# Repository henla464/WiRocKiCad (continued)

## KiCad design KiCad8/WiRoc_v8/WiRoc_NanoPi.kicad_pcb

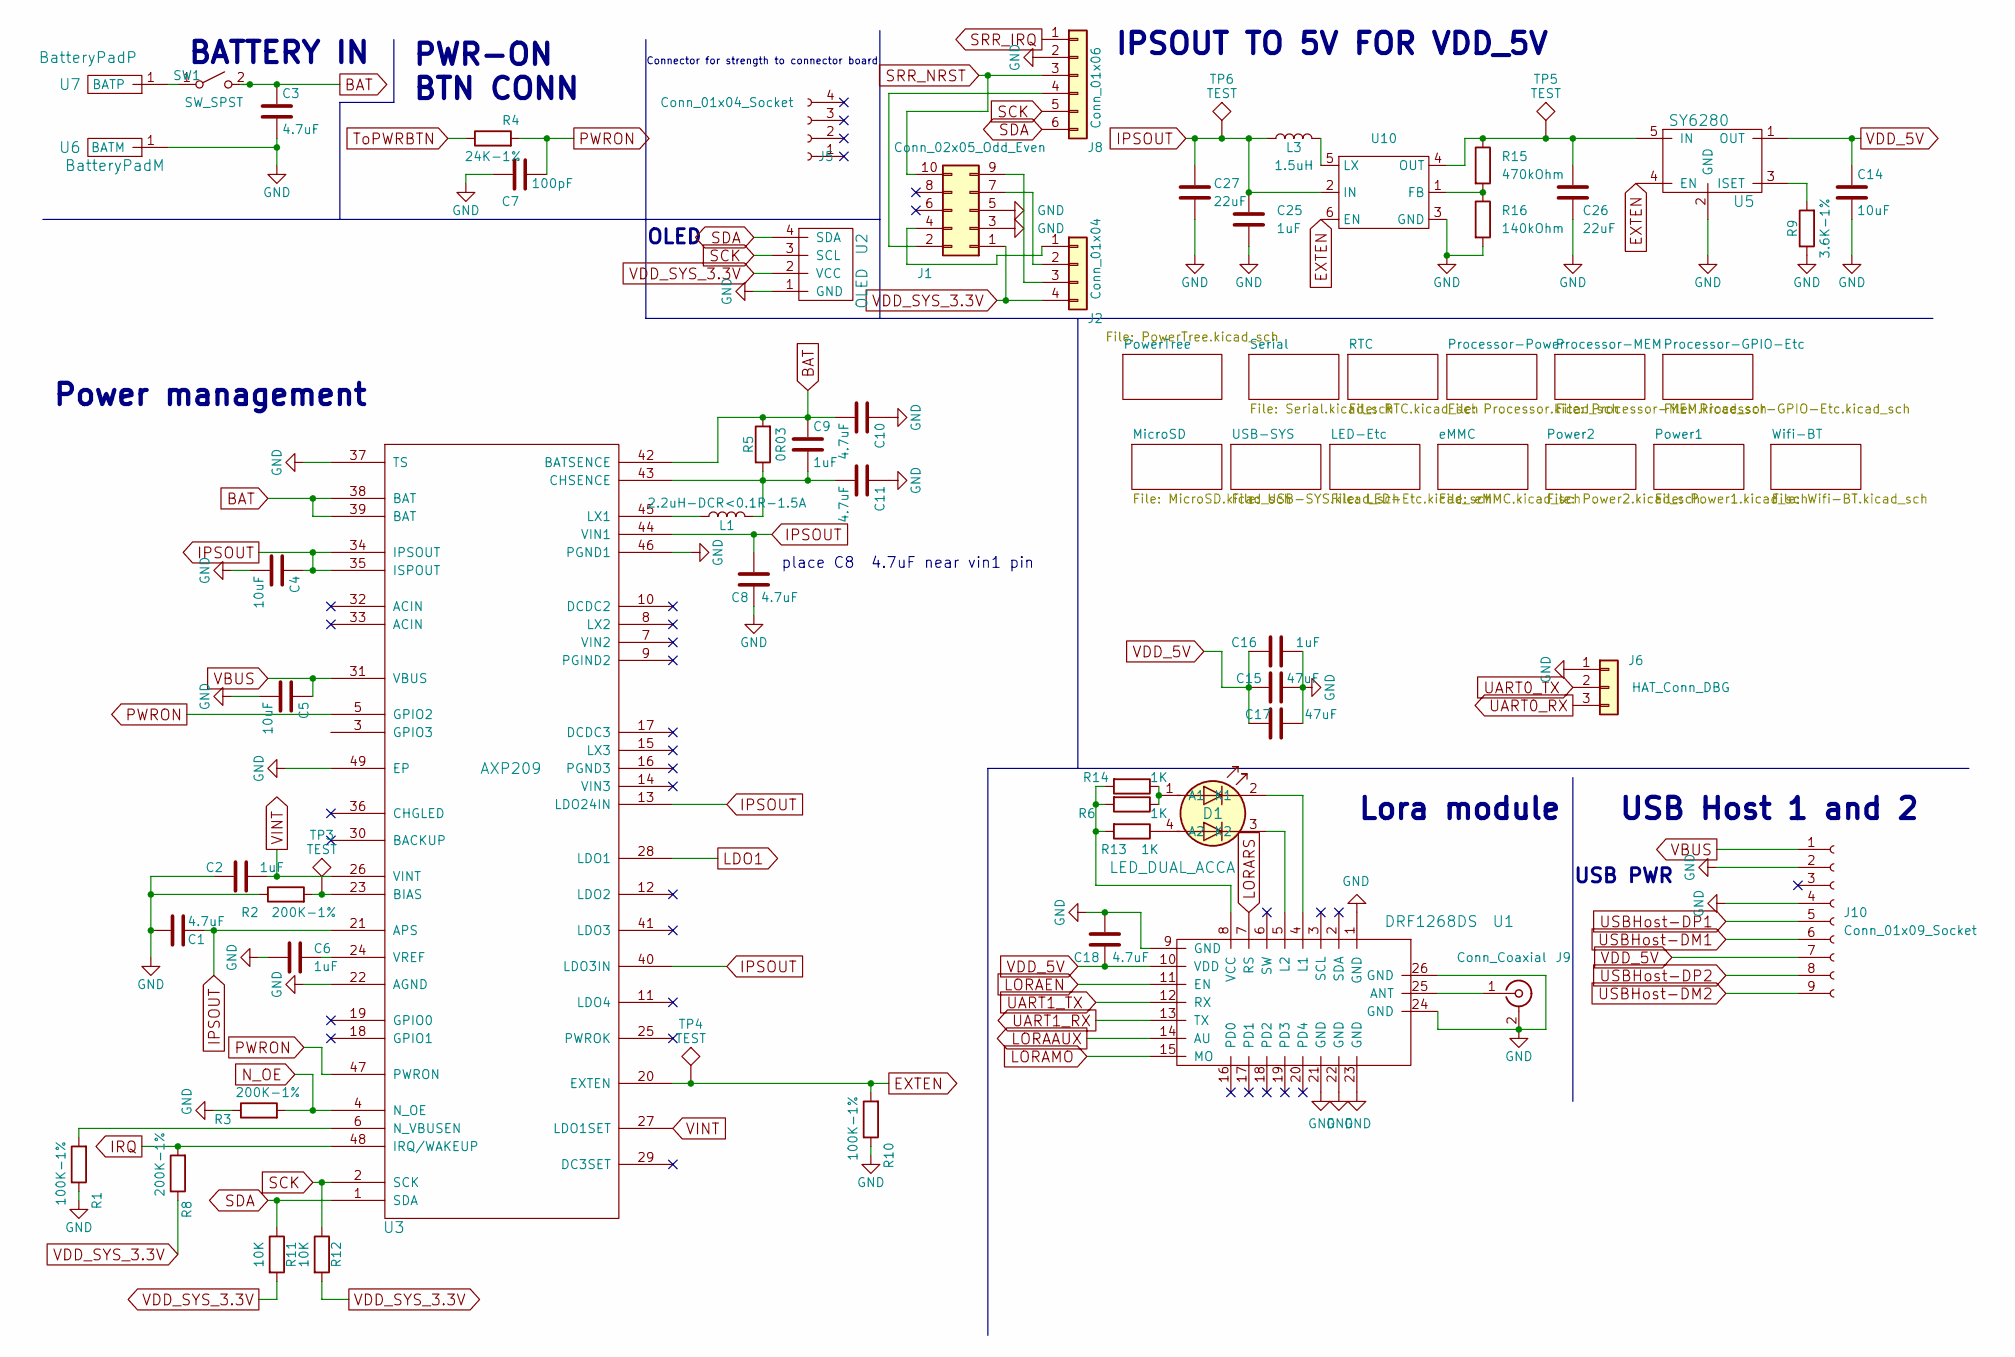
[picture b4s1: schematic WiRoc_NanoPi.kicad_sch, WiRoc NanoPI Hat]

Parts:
C1, C3, C8, C10, C11, C18: 4.7uF; C_0402_1005Metric; ManufacturerPartNumber CL10A475KO8NNNC; LCSC Part # C19666
C2, C6, C9, C16, C25: 1uF; C_0402_1005Metric; ManufacturerPartNumber CL10A105KB8NNNC; LCSC Part # C15849
C4, C5, C14: 10uF; C_0402_1005Metric; ManufacturerPartNumber CL10A106KP8NNNC; LCSC Part # C19702
C7: 100pF; C_0402_1005Metric; ManufacturerPartNumber CL10C101JB8NNNC; LCSC Part # C14858
C15, C17: 47uF; C_1206_3216Metric; ManufacturerPartNumber CL31A476MPHNNNE; LCSC Part # C96123
C26, C27: 22uF; C_0402_1005Metric; PartNo GRM188R61A226ME15D; LCSC Part # C84419
D1: LED_DUAL_ACCA; LED_Dual_1.7_1.6; ManufacturerPartNumber HL-PCB-1617S9FH203BC; LCSC Part # C513363
J1: Conn_02x05_Odd_Even; PinHeader_2x05_P1.27mm_Vertical
J2: Conn_01x04; PinHeader_1x04_P1.27mm_Horizontal
J5: Conn_01x04_Socket; PinSocket_1x04_P1.27mm_Vertical
J6: HAT_Conn_DBG; Pin_Header_Straight_1x03_Pitch2.54mm; ManufacturerPartNumber 2.54mm 1x40P
J8: Conn_01x06; PinHeader_1x06_P1.27mm_Horizontal
J9: Conn_Coaxial; SMA_Amphenol_901-143_Horizontal
J10: Conn_01x09_Socket; PinSocket_1x09_P1.27mm_Vertical
L1: 2.2uH-DCR<0.1R-1.5A; Inductor_SLW4018; ManufacturerPartNumber SLW4018S2R2MST; LCSC Part # C206341
L3: 1.5uH; Inductor_SLW4018; PartNo SLW4020S1R5MST; LCSC Part # C206395
R1, R10: 100K-1%; R_0402_1005Metric; ManufacturerPartNumber 0603WAF1003T5E; LCSC Part # C25803
R2, R3, R8: 200K-1%; R_0402_1005Metric; ManufacturerPartNumber 0603WAF2003T5E; LCSC Part # C25811
R4: 24K-1%; R_0402_1005Metric; ManufacturerPartNumber 0603WAF2402T5E; LCSC Part # C23352
R5: 0R03; R_0805_2012Metric; ManufacturerPartNumber 0805W4F300MT5E; LCSC Part # C247605
R6, R13, R14: 1K; R_0402_1005Metric; ManufacturerPartNumber 0603WAJ0102T5E; LCSC Part # C21190
R9: 3.6K-1%; R_0402_1005Metric; ManufacturerPartNumber 0603WAF3601T5E; LCSC Part # C22980
R11, R12: 10K; R_0402_1005Metric; ManufacturerPartNumber 0603WAF1002T5E; LCSC Part # C25804
R15: 470kOhm; R_0402_1005Metric; PartNo HPCR0603F470KK9; LCSC Part # C23178
R16: 140kOhm; R_0402_1005Metric; PartNo 0603WAF140KT5E; LCSC Part # C321721
SW1: SW_SPST; Pin_Header_Straight_1x02_Pitch2.54mm; ManufacturerPartNumber 2.54mm 1x40P
TP3, TP4, TP5, TP6: TEST; TestPoint_Pad_D1.0mm
U1: DRF1268DS
U2: OLED; CONN_OLED_TWI-Socket_Strip_Straight_1x04_Pitch2.54mm; ManufacturerPartNumber 2.54mm 1x40P
U3: AXP209; qfn48_6x6mm_Pitch0.4mm; ManufacturerPartNumber AXP209; LCSC Part # C2997895
U5: SY6280; SOT-23-5; ManufacturerPartNumber SY6280AAC; LCSC Part # C55136
U6: BatteryPadM; BatteryPad
U7: BatteryPadP; BatteryPadThinner
U10: TSOT-23-6; PartNo SY7069ADC; LCSC Part # C207630

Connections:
BAT: C3.1, C9.1, C10.2, R5.2, SW1.2 (B), U3.38 (BAT), U3.39 (BAT), U3.42 (BATSENCE)
EXTEN: R10.2, TP4.1, U3.20 (EXTEN), U5.4 (EN), U10.6 (EN)
GND: C1.2, C2.2, C3.2, C4.2, C5.2, C6.2, C7.1, C8.1, C10.1, C11.1, C14.2, C15.1, C16.2, C17.1, C18.2, C25.2, C26.2, C27.2, J1.3, J1.5, J6.1, J8.2, J9.2 (Ext), J10.2, J10.4, R1.1, R2.1, R3.1, R9.1, R10.1, R16.2, U1.1 (GND), U1.9 (GND), U1.21 (GND), U1.22 (GND), U1.23 (GND), U1.24 (GND), U1.26 (GND), U2.1 (GND), U3.22 (AGND), U3.37 (TS), U3.46 (PGND1), U3.49 (EP), U5.2 (GND), U6.1 (BATM), U10.3 (GND); also elsewhere on the board
IPSOUT: C1.1, C4.1, C8.2, C25.1, C27.1, L3.1, TP6.1, U3.13 (LDO24IN), U3.21 (APS), U3.34 (IPSOUT), U3.35 (ISPOUT), U3.40 (LDO3IN), U3.44 (VIN1), U10.2 (IN)
IRQ: R8.2, U3.48 (IRQ/WAKEUP); also elsewhere on the board
LDO1: U3.28 (LDO1); also elsewhere on the board
LORAAUX: U1.14 (AU); also elsewhere on the board
LORAEN: U1.11 (EN); also elsewhere on the board
LORAMO: U1.15 (MO); also elsewhere on the board
LORARS: U1.7 (RS); also elsewhere on the board
N_OE: R3.2, U3.4 (N_OE); also elsewhere on the board
unnamed: D1.1 (A1), R6.1, R14.1
unnamed: D1.4 (A2), R13.1
unnamed: D1.2 (K1), U1.4 (L1)
unnamed: D1.3 (K2), U1.5 (L2)
unnamed: J1.2, J8.4
unnamed: J1.4, J2.1
unnamed: J1.7, J2.2
unnamed: J1.9, J2.3
unnamed: J9.1 (In), U1.25 (ANT)
unnamed: SW1.1 (A), U7.1 (BATP)
unnamed: R6.2, R13.2, R14.2, U1.8 (VCC)
unnamed: R2.2, TP3.1, U3.23 (BIAS)
unnamed: C9.2, C11.2, L1.2, R5.1, U3.43 (CHSENCE)
unnamed: L1.1, U3.45 (LX1)
unnamed: R1.2, U3.6 (N_VBUSEN)
unnamed: C6.1, U3.24 (VREF)
unnamed: R9.2, U5.3 (ISET)
unnamed: R15.2, R16.1, U10.1 (FB)
unnamed: L3.2, U10.5 (LX)
unnamed: C26.1, R15.1, TP5.1, U5.5 (IN), U10.4 (OUT)
PWRON: C7.2, R4.2, U3.5 (GPIO2), U3.47 (PWRON)
SCK: J8.5, R12.1, U2.3 (SCL), U3.2 (SCK); also elsewhere on the board
SDA: J8.6, R11.1, U2.4 (SDA), U3.1 (SDA); also elsewhere on the board
SRR_IRQ: J8.1; also elsewhere on the board
SRR_NRST: J1.10, J8.3; also elsewhere on the board
ToPWRBTN: R4.1; also elsewhere on the board
UART0_RX: J6.3; also elsewhere on the board
UART0_TX: J6.2; also elsewhere on the board
UART1_RX: U1.13 (TX); also elsewhere on the board
UART1_TX: U1.12 (RX); also elsewhere on the board
USBHost-DM1: J10.6; also elsewhere on the board
USBHost-DM2: J10.9; also elsewhere on the board
USBHost-DP1: J10.5; also elsewhere on the board
USBHost-DP2: J10.8; also elsewhere on the board
VBUS: C5.1, J10.1, U3.31 (VBUS)
VDD_5V: C14.1, C15.2, C16.1, C17.2, C18.1, J10.7, U1.10 (VDD), U5.1 (OUT); also elsewhere on the board
VDD_SYS_3.3V: J1.1, J2.4, R8.1, R11.2, R12.2, U2.2 (VCC); also elsewhere on the board
VINT: C2.1, U3.26 (VINT), U3.27 (LDO1SET)

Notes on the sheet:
place C8 4.7uF near vin1 pin
USB PWR
Lora module
IPSOUT TO 5V FOR VDD_5V
PWR-ON BTN CONN
Power management
OLED
Connector for strength to connector board
USB Host 1 and 2
BATTERY IN

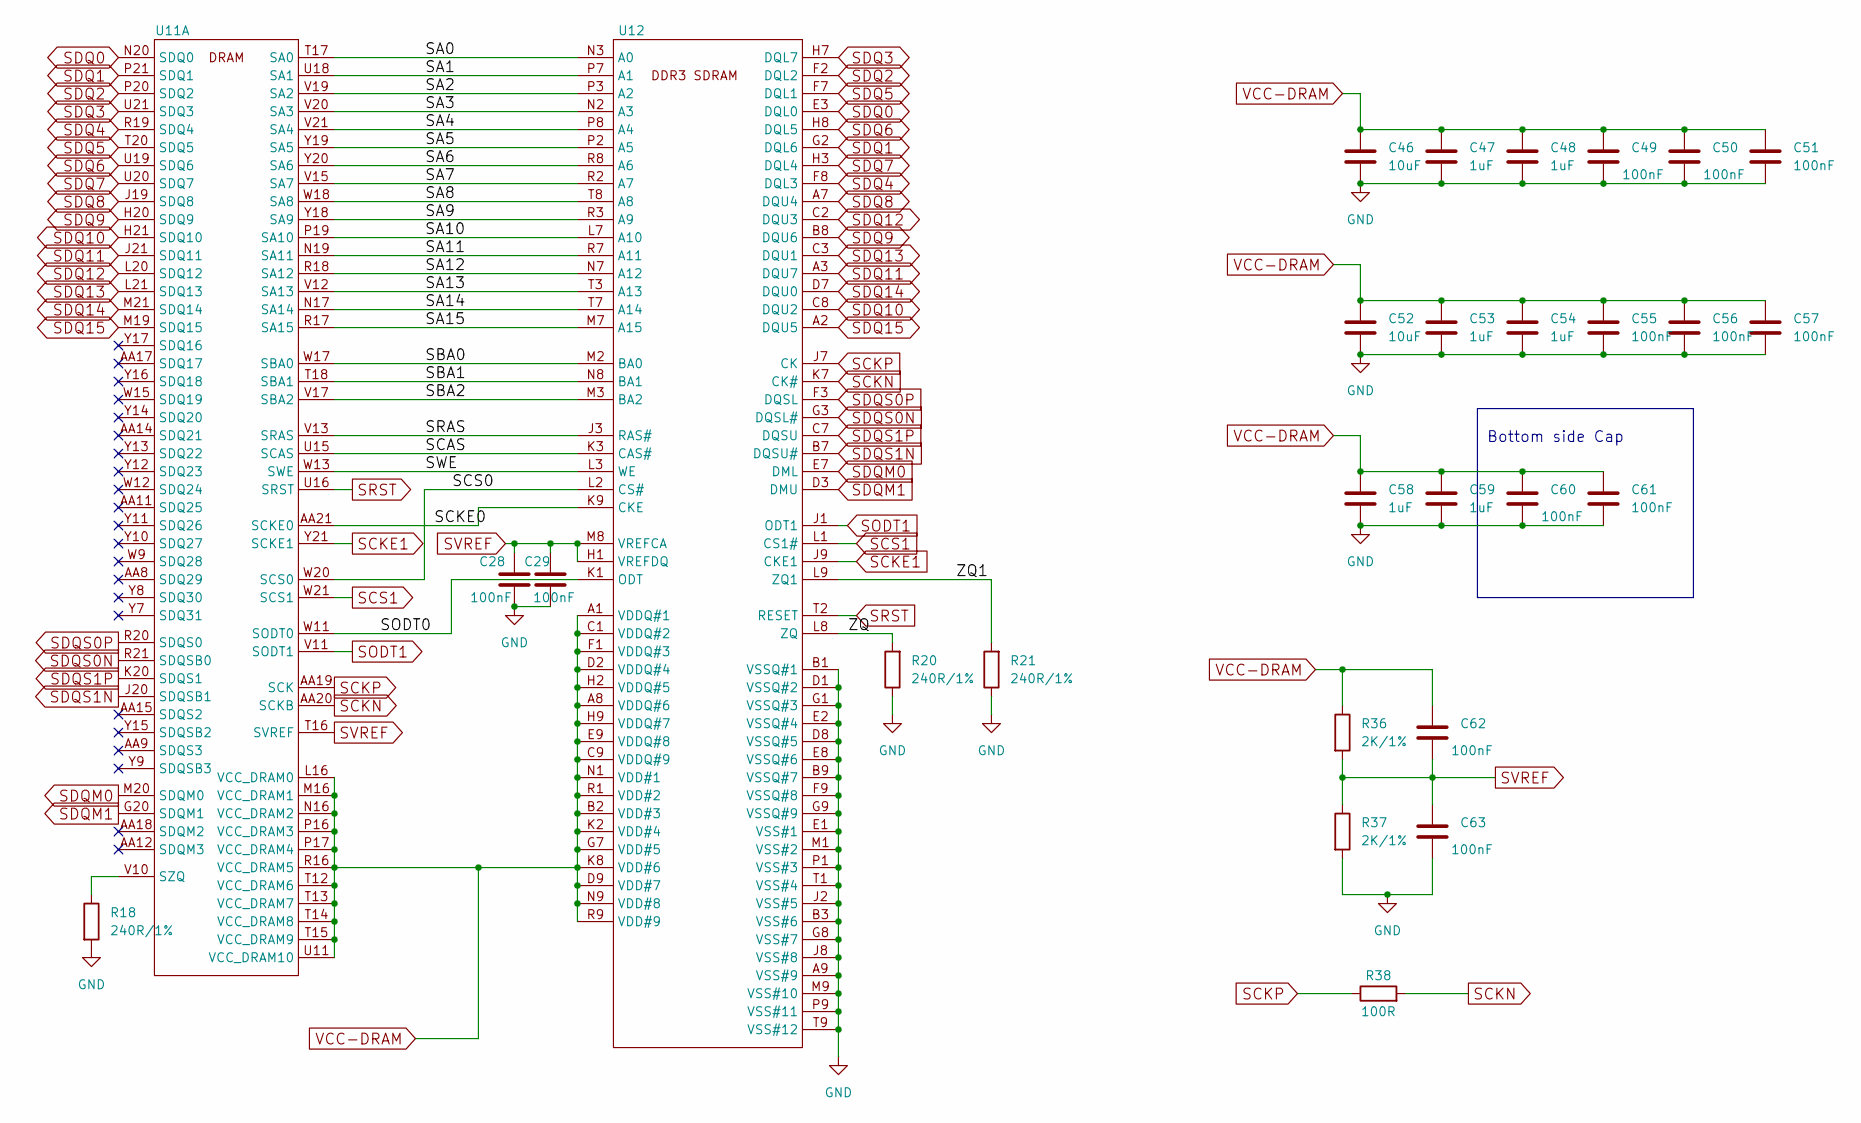
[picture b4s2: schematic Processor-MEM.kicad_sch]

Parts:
C28, C29, C49, C50, C51, C55, C56, C57, C60, C61, C62, C63: 100nF; C_0402_1005Metric
C46, C52: 10uF; C_0402_1005Metric
C47, C48, C53, C54, C58, C59: 1uF; C_0402_1005Metric
R18, R20, R21: 240R/1%; R_0402_1005Metric
R36, R37: 2K/1%; R_0402_1005Metric
R38: 100R; R_0402_1005Metric
U11: BGA-347_21x21_14.0x14.0mm
U12: BGA-96_9.0x13.0mm_Layout2x3x16_P0.8mm

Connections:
/Processor-MEM/SA0: U11.T17 (SA0), U12.N3 (A0)
/Processor-MEM/SA1: U11.U18 (SA1), U12.P7 (A1)
/Processor-MEM/SA2: U11.V19 (SA2), U12.P3 (A2)
/Processor-MEM/SA3: U11.V20 (SA3), U12.N2 (A3)
/Processor-MEM/SA4: U11.V21 (SA4), U12.P8 (A4)
/Processor-MEM/SA5: U11.Y19 (SA5), U12.P2 (A5)
/Processor-MEM/SA6: U11.Y20 (SA6), U12.R8 (A6)
/Processor-MEM/SA7: U11.V15 (SA7), U12.R2 (A7)
/Processor-MEM/SA8: U11.W18 (SA8), U12.T8 (A8)
/Processor-MEM/SA9: U11.Y18 (SA9), U12.R3 (A9)
/Processor-MEM/SA10: U11.P19 (SA10), U12.L7 (A10)
/Processor-MEM/SA11: U11.N19 (SA11), U12.R7 (A11)
/Processor-MEM/SA12: U11.R18 (SA12), U12.N7 (A12)
/Processor-MEM/SA13: U11.V12 (SA13), U12.T3 (A13)
/Processor-MEM/SA14: U11.N17 (SA14), U12.T7 (A14)
/Processor-MEM/SA15: U11.R17 (SA15), U12.M7 (A15)
/Processor-MEM/SBA0: U11.W17 (SBA0), U12.M2 (BA0)
/Processor-MEM/SBA1: U11.T18 (SBA1), U12.N8 (BA1)
/Processor-MEM/SBA2: U11.V17 (SBA2), U12.M3 (BA2)
/Processor-MEM/SCAS: U11.U15 (SCAS), U12.K3 (CAS#)
/Processor-MEM/SCKE0: U11.AA21 (SCKE0), U12.K9 (CKE)
/Processor-MEM/SCS0: U11.W20 (SCS0), U12.L2 (CS#)
/Processor-MEM/SODT0: U11.W11 (SODT0), U12.K1 (ODT)
/Processor-MEM/SRAS: U11.V13 (SRAS), U12.J3 (RAS#)
/Processor-MEM/SWE: U11.W13 (SWE), U12.L3 (WE)
/Processor-MEM/ZQ: R20.2, U12.L8 (ZQ)
/Processor-MEM/ZQ1: R21.2, U12.L9 (ZQ1)
GND: C28.2, C29.2, C46.2, C47.2, C48.2, C49.2, C50.2, C51.2, C52.2, C53.2, C54.2, C55.2, C56.2, C57.2, C58.2, C59.2, C60.2, C61.2, C63.2, R18.2, R20.1, R21.1, R37.2, U12.A9 (VSS#9), U12.B1 (VSSQ#1), U12.B3 (VSS#6), U12.B9 (VSSQ#7), U12.D1 (VSSQ#2), U12.D8 (VSSQ#5), U12.E1 (VSS#1), U12.E2 (VSSQ#4), U12.E8 (VSSQ#6), U12.F9 (VSSQ#8), U12.G1 (VSSQ#3), U12.G8 (VSS#7), U12.G9 (VSSQ#9), U12.J2 (VSS#5), U12.J8 (VSS#8), U12.M1 (VSS#2), U12.M9 (VSS#10), U12.P1 (VSS#3), U12.P9 (VSS#11), U12.T1 (VSS#4), U12.T9 (VSS#12); also elsewhere on the board
unnamed: R18.1, U11.V10 (SZQ)
SCKE1: U11.Y21 (SCKE1), U12.J9 (CKE1)
SCKN: R38.2, U11.AA20 (SCKB), U12.K7 (CK#)
SCKP: R38.1, U11.AA19 (SCK), U12.J7 (CK)
SCS1: U11.W21 (SCS1), U12.L1 (CS1#)
SDQ0: U11.N20 (SDQ0), U12.E3 (DQL0)
SDQ1: U11.P21 (SDQ1), U12.G2 (DQL6)
SDQ2: U11.P20 (SDQ2), U12.F2 (DQL2)
SDQ3: U11.U21 (SDQ3), U12.H7 (DQL7)
SDQ4: U11.R19 (SDQ4), U12.F8 (DQL3)
SDQ5: U11.T20 (SDQ5), U12.F7 (DQL1)
SDQ6: U11.U19 (SDQ6), U12.H8 (DQL5)
SDQ7: U11.U20 (SDQ7), U12.H3 (DQL4)
SDQ8: U11.J19 (SDQ8), U12.A7 (DQU4)
SDQ9: U11.H20 (SDQ9), U12.B8 (DQU6)
SDQ10: U11.H21 (SDQ10), U12.C8 (DQU2)
SDQ11: U11.J21 (SDQ11), U12.A3 (DQU7)
SDQ12: U11.L20 (SDQ12), U12.C2 (DQU3)
SDQ13: U11.L21 (SDQ13), U12.C3 (DQU1)
SDQ14: U11.M21 (SDQ14), U12.D7 (DQU0)
SDQ15: U11.M19 (SDQ15), U12.A2 (DQU5)
SDQM0: U11.M20 (SDQM0), U12.E7 (DML)
SDQM1: U11.G20 (SDQM1), U12.D3 (DMU)
SDQS0N: U11.R21 (SDQSB0), U12.G3 (DQSL#)
SDQS0P: U11.R20 (SDQS0), U12.F3 (DQSL)
SDQS1N: U11.J20 (SDQSB1), U12.B7 (DQSU#)
SDQS1P: U11.K20 (SDQS1), U12.C7 (DQSU)
SODT1: U11.V11 (SODT1), U12.J1 (ODT1)
SRST: U11.U16 (SRST), U12.T2 (RESET)
SVREF: C28.1, C29.1, C62.2, C63.1, R36.2, R37.1, U11.T16 (SVREF), U12.H1 (VREFDQ), U12.M8 (VREFCA)
VCC-DRAM: C46.1, C47.1, C48.1, C49.1, C50.1, C51.1, C52.1, C53.1, C54.1, C55.1, C56.1, C57.1, C58.1, C59.1, C60.1, C61.1, C62.1, R36.1, U11.L16 (VCC_DRAM0), U11.M16 (VCC_DRAM1), U11.N16 (VCC_DRAM2), U11.P16 (VCC_DRAM3), U11.P17 (VCC_DRAM4), U11.R16 (VCC_DRAM5), U11.T12 (VCC_DRAM6), U11.T13 (VCC_DRAM7), U11.T14 (VCC_DRAM8), U11.T15 (VCC_DRAM9), U11.U11 (VCC_DRAM10), U12.A1 (VDDQ#1), U12.A8 (VDDQ#6), U12.B2 (VDD#3), U12.C1 (VDDQ#2), U12.C9 (VDDQ#9), U12.D2 (VDDQ#4), U12.D9 (VDD#7), U12.E9 (VDDQ#8), U12.F1 (VDDQ#3), U12.G7 (VDD#5), U12.H2 (VDDQ#5), U12.H9 (VDDQ#7), U12.K2 (VDD#4), U12.K8 (VDD#6), U12.N1 (VDD#1), U12.N9 (VDD#8), U12.R1 (VDD#2), U12.R9 (VDD#9); also elsewhere on the board

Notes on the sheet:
Bottom side Cap

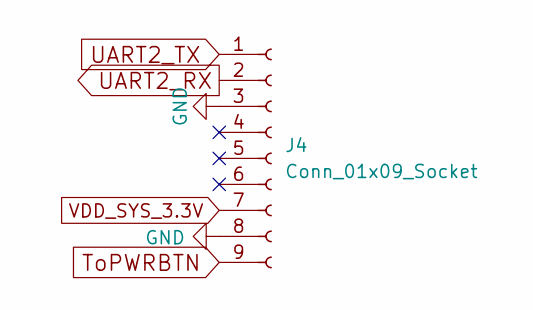
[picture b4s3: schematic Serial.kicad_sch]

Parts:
J4: Conn_01x09_Socket; PinSocket_1x09_P1.27mm_Vertical

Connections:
GND: J4.3, J4.8; also elsewhere on the board
ToPWRBTN: J4.9; also elsewhere on the board
UART2_RX: J4.2; also elsewhere on the board
UART2_TX: J4.1; also elsewhere on the board
VDD_SYS_3.3V: J4.7; also elsewhere on the board

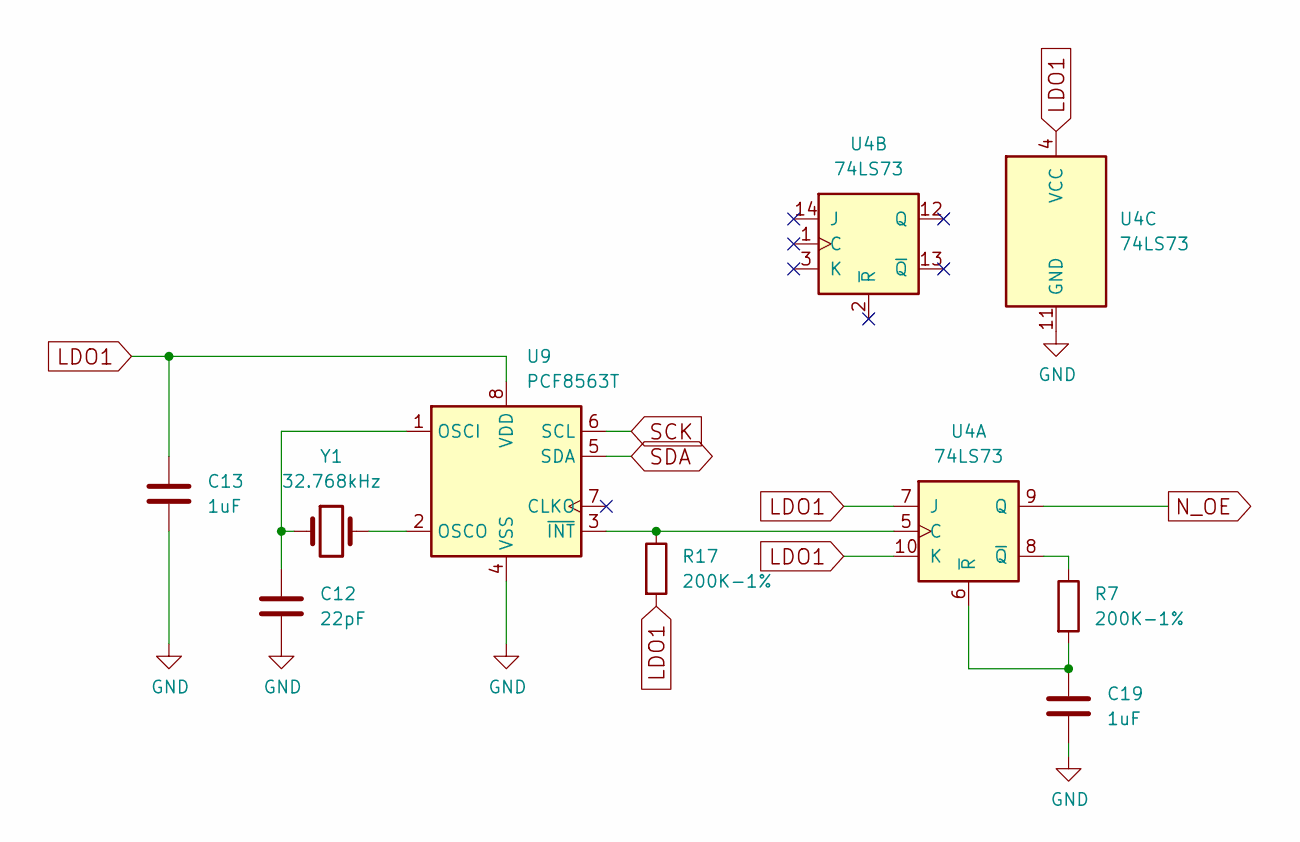
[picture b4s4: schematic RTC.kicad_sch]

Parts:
C12: 22pF; C_0402_1005Metric; ManufacturerPartNumber GRM155R71C223JA01D; LCSC Part # C1555
C13, C19: 1uF; C_0402_1005Metric; ManufacturerPartNumber CL10A105KB8NNNC; LCSC Part # C15849
R7, R17: 200K-1%; R_0402_1005Metric; ManufacturerPartNumber 0603WAF2003T5E; LCSC Part # C25811
U4: 74LS73; SOIC-14_3.9x8.7mm_P1.27mm; ManufacturerPartNumber CD74HC73M96; LCSC Part # C350539
U9: PCF8563T; SOIC-8_3.9x4.9mm_P1.27mm; ManufacturerPartNumber PCF8563T/5,518; LCSC Part # C7440
Y1: 32.768kHz; SMD3215-2P; ManufacturerPartNumber Q13FC1350000400; LCSC Part # C32346

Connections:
GND: C12.2, C13.2, C19.2, U4.11 (GND), U9.4 (VSS); also elsewhere on the board
LDO1: C13.1, R17.2, U4.4 (VCC), U4.7 (J), U4.10 (K), U9.8 (VDD); also elsewhere on the board
N_OE: U4.9 (Q); also elsewhere on the board
unnamed: R17.1, U4.5 (C), U9.3 (~INT)
unnamed: R7.1, U4.8 (~Q)
unnamed: C19.1, R7.2, U4.6 (~R)
unnamed: C12.1, U9.1 (OSCI), Y1.1
unnamed: U9.2 (OSCO), Y1.2
SCK: U9.6 (SCL); also elsewhere on the board
SDA: U9.5 (SDA); also elsewhere on the board

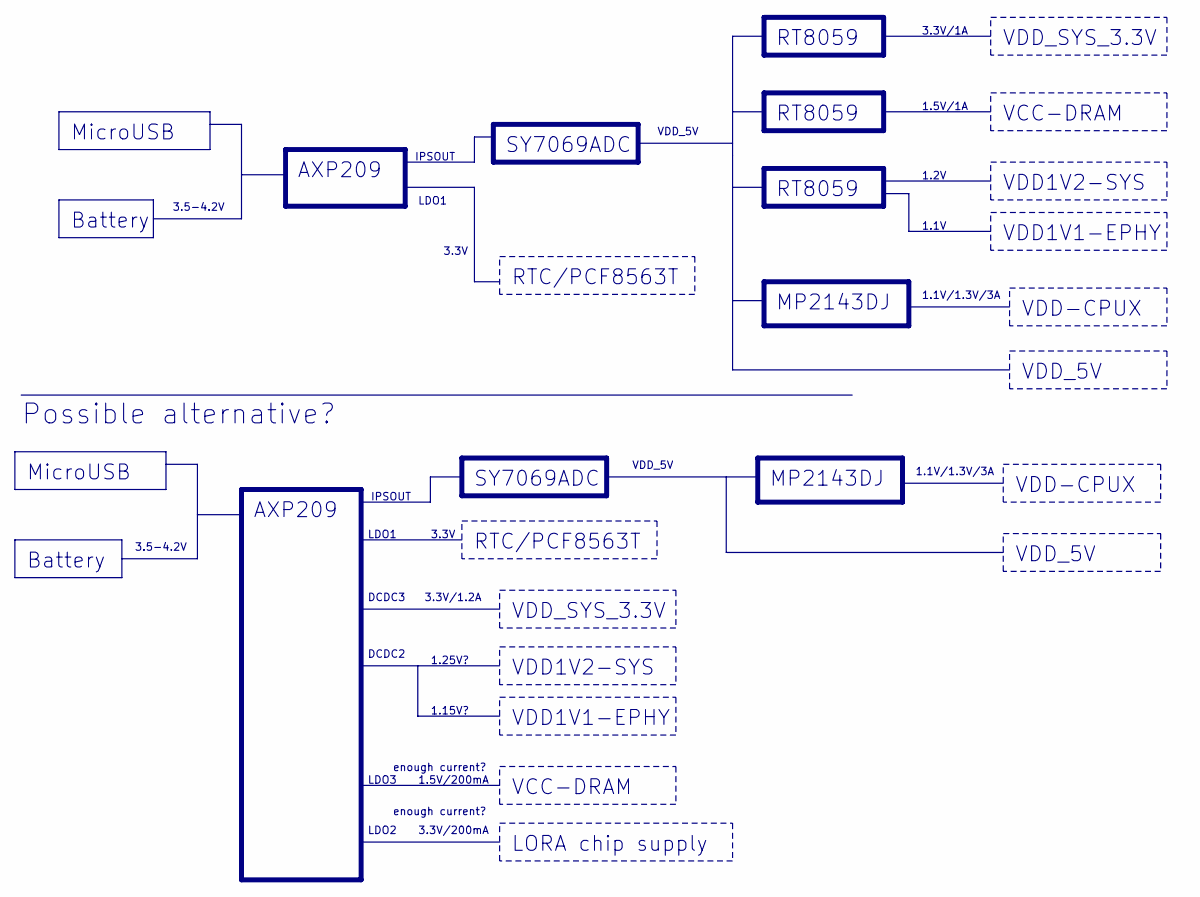
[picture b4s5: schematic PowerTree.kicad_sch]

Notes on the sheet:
VDD1V1-EPHY
VDD-CPUX
MicroUSB
RTC/PCF8563T
SY7069ADC
Battery
VDD1V2-SYS
MP2143DJ
RT8059
VDD_SYS_3.3V
VDD_5V
AXP209
VCC-DRAM
LORA chip supply
1.5V/1A
3.5-4.2V
DCDC3
1.1V/1.3V/3A
Possible alternative?
3.3V/1.2A
1.5V/200mA
1.25V?
IPSOUT
LDO2
3.3V/1A
3.3V/200mA
1.2V
1.15V?
DCDC2
LDO1
LDO3
3.3V
1.1V
enough current?

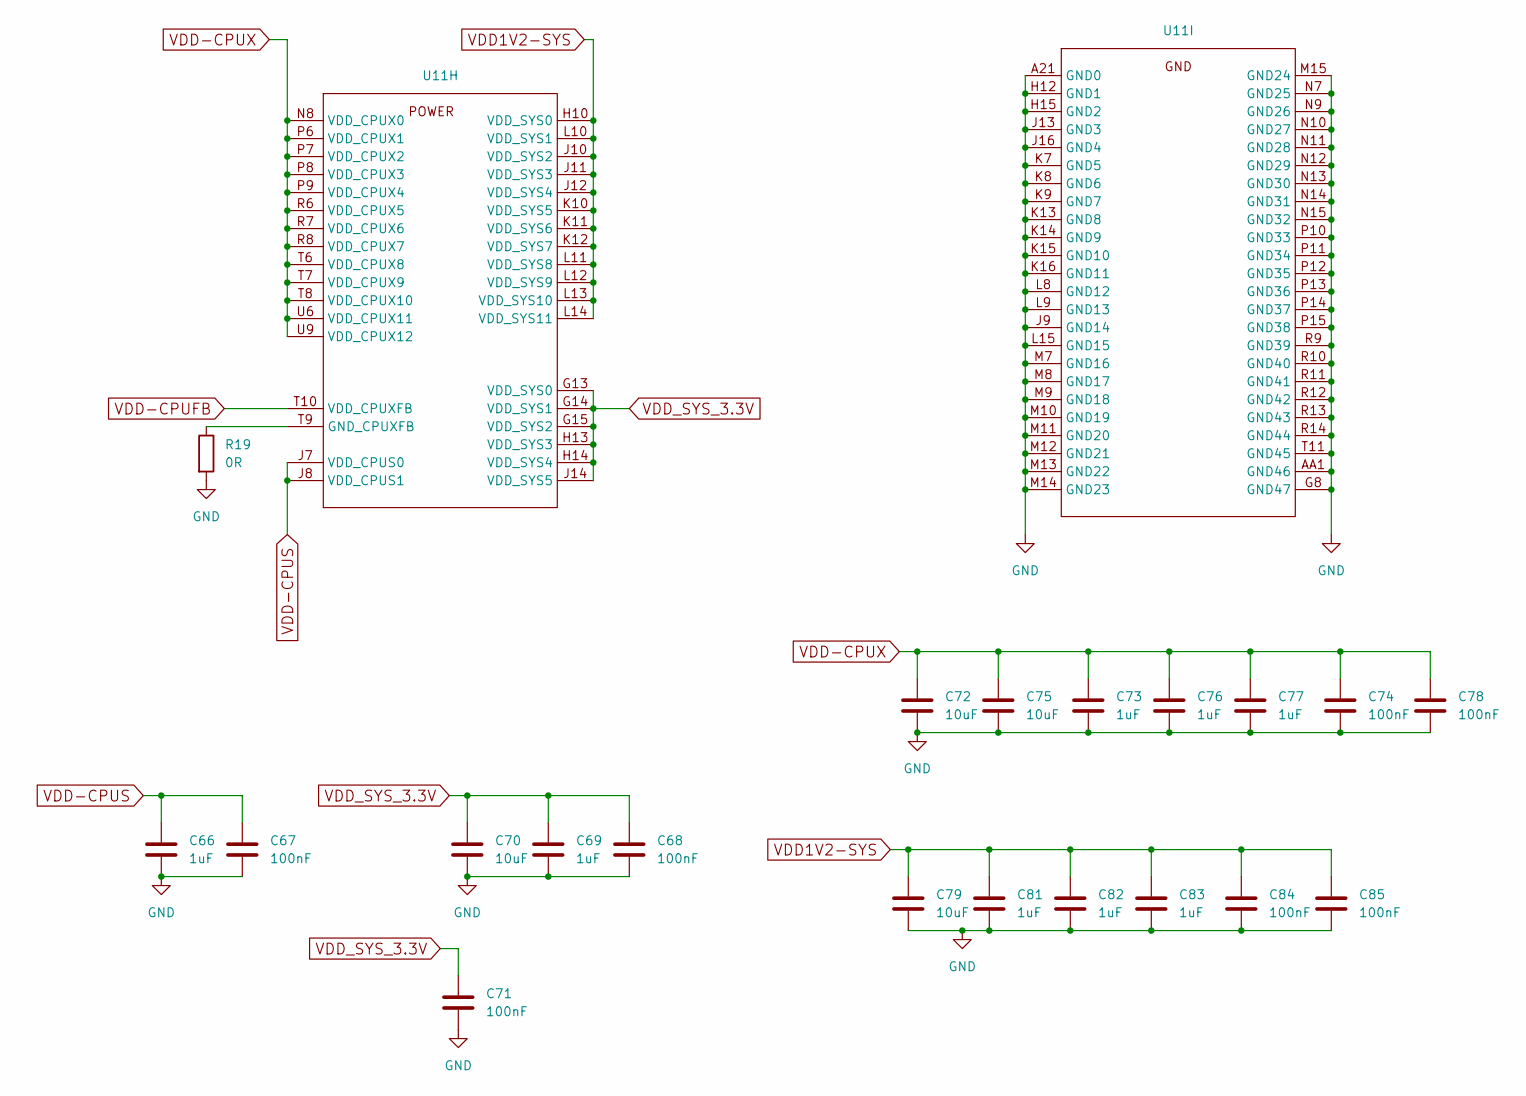
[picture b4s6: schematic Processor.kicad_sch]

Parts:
C66, C69, C73, C76, C77, C81, C82, C83: 1uF; C_0402_1005Metric
C67, C68, C71, C74, C78, C84, C85: 100nF; C_0402_1005Metric
C70, C72, C75, C79: 10uF; C_0402_1005Metric
R19: 0R; R_0402_1005Metric
U11: BGA-347_21x21_14.0x14.0mm

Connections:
GND: C66.2, C67.2, C68.2, C69.2, C70.2, C71.2, C72.2, C73.2, C74.2, C75.2, C76.2, C77.2, C78.2, C79.2, C81.2, C82.2, C83.2, C84.2, C85.2, R19.2, U11.A21 (GND0), U11.AA1 (GND46), U11.G8 (GND47), U11.H12 (GND1), U11.H15 (GND2), U11.J9 (GND14), U11.J13 (GND3), U11.J16 (GND4), U11.K7 (GND5), U11.K8 (GND6), U11.K9 (GND7), U11.K13 (GND8), U11.K14 (GND9), U11.K15 (GND10), U11.K16 (GND11), U11.L8 (GND12), U11.L9 (GND13), U11.L15 (GND15), U11.M7 (GND16), U11.M8 (GND17), U11.M9 (GND18), U11.M10 (GND19), U11.M11 (GND20), U11.M12 (GND21), U11.M13 (GND22), U11.M14 (GND23), U11.M15 (GND24), U11.N7 (GND25), U11.N9 (GND26), U11.N10 (GND27), U11.N11 (GND28), U11.N12 (GND29), U11.N13 (GND30), U11.N14 (GND31), U11.N15 (GND32), U11.P10 (GND33), U11.P11 (GND34), U11.P12 (GND35), U11.P13 (GND36), U11.P14 (GND37), U11.P15 (GND38), U11.R9 (GND39), U11.R10 (GND40), U11.R11 (GND41), U11.R12 (GND42), U11.R13 (GND43), U11.R14 (GND44), U11.T11 (GND45); also elsewhere on the board
unnamed: R19.1, U11.T9 (GND_CPUXFB)
VDD1V2-SYS: C79.1, C81.1, C82.1, C83.1, C84.1, C85.1, U11.H10 (VDD_SYS0), U11.J10 (VDD_SYS2), U11.J11 (VDD_SYS3), U11.J12 (VDD_SYS4), U11.K10 (VDD_SYS5), U11.K11 (VDD_SYS6), U11.K12 (VDD_SYS7), U11.L10 (VDD_SYS1), U11.L11 (VDD_SYS8), U11.L12 (VDD_SYS9), U11.L13 (VDD_SYS10), U11.L14 (VDD_SYS11); also elsewhere on the board
VDD-CPUFB: U11.T10 (VDD_CPUXFB); also elsewhere on the board
VDD-CPUS: C66.1, C67.1, U11.J7 (VDD_CPUS0), U11.J8 (VDD_CPUS1); also elsewhere on the board
VDD-CPUX: C72.1, C73.1, C74.1, C75.1, C76.1, C77.1, C78.1, U11.N8 (VDD_CPUX0), U11.P6 (VDD_CPUX1), U11.P7 (VDD_CPUX2), U11.P8 (VDD_CPUX3), U11.P9 (VDD_CPUX4), U11.R6 (VDD_CPUX5), U11.R7 (VDD_CPUX6), U11.R8 (VDD_CPUX7), U11.T6 (VDD_CPUX8), U11.T7 (VDD_CPUX9), U11.T8 (VDD_CPUX10), U11.U6 (VDD_CPUX11), U11.U9 (VDD_CPUX12); also elsewhere on the board
VDD_SYS_3.3V: C68.1, C69.1, C70.1, C71.1, U11.G13 (VDD_SYS0), U11.G14 (VDD_SYS1), U11.G15 (VDD_SYS2), U11.H13 (VDD_SYS3), U11.H14 (VDD_SYS4), U11.J14 (VDD_SYS5); also elsewhere on the board

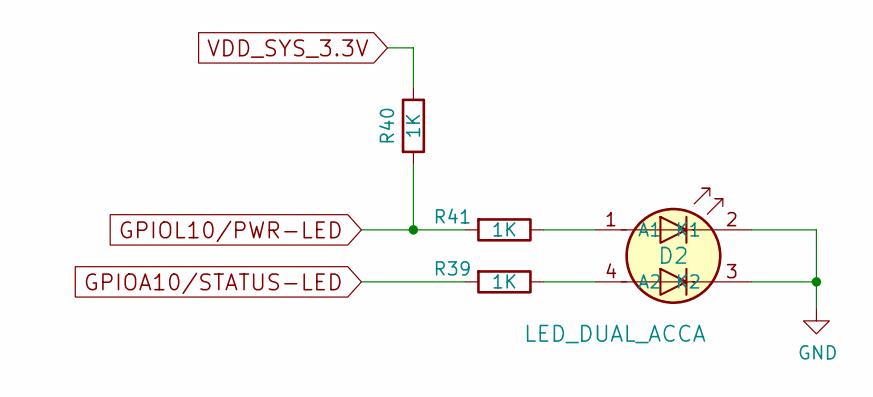
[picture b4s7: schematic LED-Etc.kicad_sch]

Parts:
D2: LED_DUAL_ACCA; LED_Dual_1.7_1.6; ManufacturerPartNumber HL-PCB-1617S9FH203BC; LCSC Part # C513363
R39, R40, R41: 1K; R_0402_1005Metric; ManufacturerPartNumber 0603WAJ0102T5E; LCSC Part # C21190

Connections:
GPIOA10/STATUS-LED: R39.2; also elsewhere on the board
GND: D2.2 (K1), D2.3 (K2); also elsewhere on the board
GPIOL10/PWR-LED: R40.2, R41.2; also elsewhere on the board
unnamed: D2.1 (A1), R41.1
unnamed: D2.4 (A2), R39.1
VDD_SYS_3.3V: R40.1; also elsewhere on the board

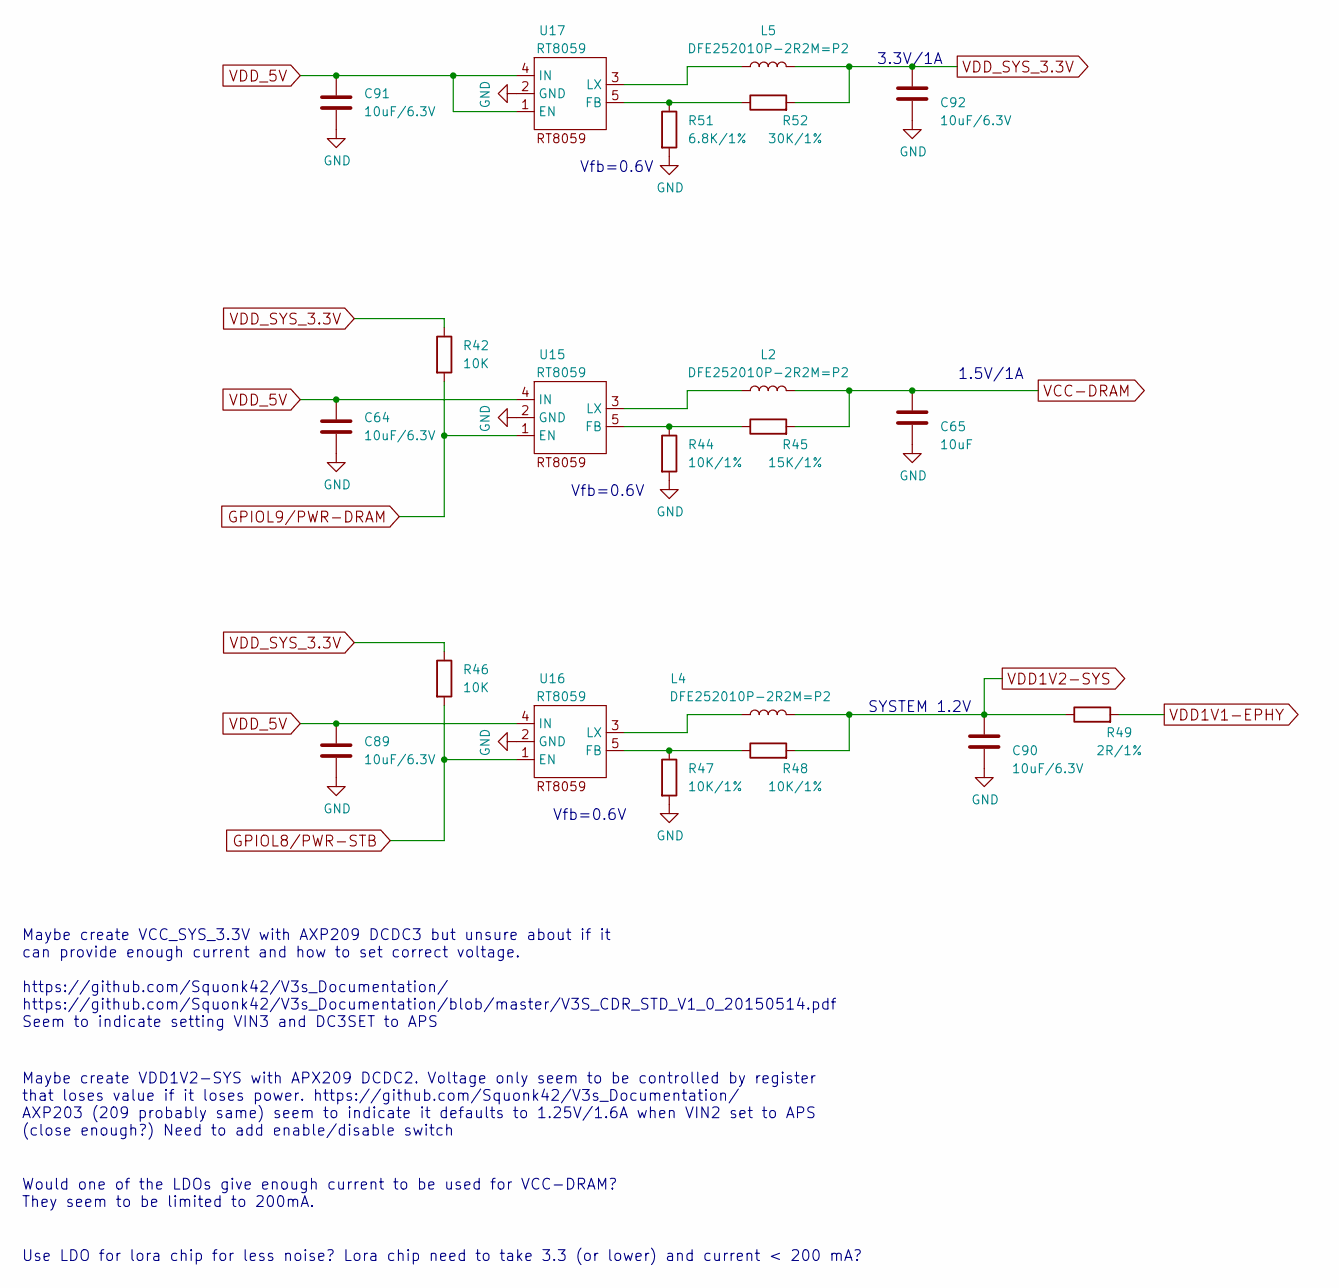
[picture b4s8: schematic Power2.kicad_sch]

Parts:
C64, C89, C90, C91, C92: 10uF/6.3V; C_0402_1005Metric
C65: 10uF; C_0402_1005Metric
L2, L4, L5: DFE252010P-2R2M=P2; L_1008_2520Metric
R42, R46: 10K; R_0402_1005Metric
R44, R47, R48: 10K/1%; R_0402_1005Metric
R45: 15K/1%; R_0402_1005Metric
R49: 2R/1%; R_0402_1005Metric
R51: 6.8K/1%; R_0402_1005Metric
R52: 30K/1%; R_0402_1005Metric
U15, U16, U17: RT8059; TSOT-23-5

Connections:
GND: C64.2, C65.2, C89.2, C90.2, C91.2, C92.2, R44.2, R47.2, R51.2, U15.2 (GND), U16.2 (GND), U17.2 (GND); also elsewhere on the board
GPIOL8/PWR-STB: R46.2, U16.1 (EN); also elsewhere on the board
GPIOL9/PWR-DRAM: R42.2, U15.1 (EN); also elsewhere on the board
unnamed: R44.1, R45.1, U15.5 (FB)
unnamed: L2.1, U15.3 (LX)
unnamed: R47.1, R48.1, U16.5 (FB)
unnamed: L4.1, U16.3 (LX)
unnamed: R51.1, R52.1, U17.5 (FB)
unnamed: L5.1, U17.3 (LX)
VCC-DRAM: C65.1, L2.2, R45.2; also elsewhere on the board
VDD1V1-EPHY: R49.2; also elsewhere on the board
VDD1V2-SYS: C90.1, L4.2, R48.2, R49.1; also elsewhere on the board
VDD_5V: C64.1, C89.1, C91.1, U15.4 (IN), U16.4 (IN), U17.1 (EN), U17.4 (IN); also elsewhere on the board
VDD_SYS_3.3V: C92.1, L5.2, R42.1, R46.1, R52.2; also elsewhere on the board

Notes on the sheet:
Vfb=0.6V
Maybe create VDD1V2-SYS with APX209 DCDC2. Voltage only seem to be controlled by register that loses value if it loses power. https://github.com/Squonk42/V3s_Documentation/ AXP203 (209 probably same) seem to indicate it defaults to 1.25V/1.6A when VIN2 set to APS (close enough?) Need to add enable/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
1.5V/1A
Maybe create VCC_SYS_3.3V with AXP209 DCDC3 but unsure about if it can provide enough current and how to set correct voltage. https://github.com/Squonk42/V3s_Documentation/ https://github.com/Squonk42/V3s_Documentation/blob/master/V3S_CDR_STD_V1_0_20150514.pdf Seem to indicate setting VIN3 and DC3S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
Would one of the LDOs give enough current to be used for VCC-DRAM? They seem to be limited to 200mA.
Use LDO for lora chip for less noise? Lora chip need to take 3.3 (or lower) and current < 200 mA?
3.3V/1A
SYSTEM 1.2V

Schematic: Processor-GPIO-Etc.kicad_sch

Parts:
C45: 100nF; C_0402_1005Metric
R25: 4,7K; R_0402_1005Metric
R33, R35: 10K; R_0402_1005Metric
R34: 22R; R_0402_1005Metric
U11: BGA-347_21x21_14.0x14.0mm

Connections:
GPIOA10/STATUS-LED: U11.E11 (PA10/SIM_DET/PA_EINT10); also elsewhere on the board
GND: C45.2, R33.2; also elsewhere on the board
IRQ: U11.E13 (PA3/UART2_CTS/JTAG_DI0/PA_EINT3); also elsewhere on the board
LORAAUX: U11.C3 (PG8/UART1_RTS/PG_EINT8); also elsewhere on the board
LORAEN: U11.D6 (PA2/UART2_RTS/JTAG_DO0/PA_EINT2); also elsewhere on the board
LORAMO: U11.C14 (PA17/SPDIF_OUT/PA_EINT17); also elsewhere on the board
unnamed: R33.1, U11.F16 (PC4/NAND_CE0)
unnamed: R34.1, U11.A17 (PC5/NAND_RE/SDC2_CLK)
unnamed: R35.1, U11.A16 (PC7/NAND_RB1)
unnamed: R25.2, U11.H6 (PA5/UART0_RX/PWM0/PA_EINT5)
SCK: U11.F11 (PA11/TWI0_SCK/DI_TX/PA_EINT11); also elsewhere on the board
SDA: U11.C13 (PA12/TWI0_SDA/DI_RX/PA_EINT12); also elsewhere on the board
SDC0-CLK: U11.D20 (PF2/SDC0_CLK/UART0_TX); also elsewhere on the board
SDC0-CMD: U11.F18 (PF3/SDC0_CMD/JTAG_DO0); also elsewhere on the board
SDC0-D0: U11.A19 (PF1/SDC0_D0/JTAG_DI0); also elsewhere on the board
SDC0-D1: U11.D19 (PF0/SDC0_D1/JTAG_MS0); also elsewhere on the board
SDC0-D2: U11.C20 (PF5/SDC0_D2/JTAG_CK0); also elsewhere on the board
SDC0-D3: U11.E21 (PF4/SDC0_D3/UART0_RX); also elsewhere on the board
SDC0-DET: U11.G18 (PF6); also elsewhere on the board
SRR_IRQ: U11.E14 (PA6/SIM_PWREN/PA_EINT6); also elsewhere on the board
SRR_NRST: U11.E3 (PG9/UART1_CTS/PG_EINT9); also elsewhere on the board
UART0_RX: R25.1; also elsewhere on the board
UART0_TX: U11.F5 (PA4/UART0_TX/PA_EINT4); also elsewhere on the board
UART1_RX: U11.D3 (PG7/UART1_RX/PG_EINT7); also elsewhere on the board
UART1_TX: U11.G4 (PG6/UART1_TX/PG_EINT6); also elsewhere on the board
UART2_RX: U11.D5 (PA1/UART2_RX/JTAG_CK0/PA_EINT1); also elsewhere on the board
UART2_TX: U11.D11 (PA0/UART2_TX/JTAG_MS0/PA_EINT0); also elsewhere on the board
VDD_SYS_3.3V: C45.1, R35.2, U11.H7 (VCC_PG), U11.J15 (VCC-PD); also elsewhere on the board
WIFI-DataReady: U11.L18 (PD16/MDC); also elsewhere on the board
WIFI-EN: U11.D2 (PG11/PCM1_CLK/PG_EINT11); also elsewhere on the board
WIFI-HandShake: U11.L19 (PD17/MDIO); also elsewhere on the board
WIFI-SPI-CS0: U11.B15 (PC3/NAND_CE1/SPI0_CS); also elsewhere on the board
WIFI-SPI-MISO: U11.C16 (PC1/NAND_ALE/SPI0_MISO); also elsewhere on the board
WIFI-SPI-MOSI: U11.C15 (PC0/NAND_WE/SPI0_MOSI); also elsewhere on the board
WIFI-SPI-SCLK: U11.B16 (PC2/NAND_CLE/SPI0_CLK); also elsewhere on the board
eMMC-CLK: R34.2; also elsewhere on the board
eMMC-CMD: U11.E16 (PC6/NAND_RB0/SDC2_CMD); also elsewhere on the board
eMMC-D0: U11.B18 (PC8/NAND_DQ0/SDC2_D0); also elsewhere on the board
eMMC-D1: U11.C17 (PC9/NAND_DQ1/SDC2_D1); also elsewhere on the board
eMMC-D2: U11.D17 (PC10/NAND_DQ2/SDC2_D2); also elsewhere on the board
eMMC-D3: U11.C18 (PC11/NAND_DQ3/SDC2_D3); also elsewhere on the board
eMMC-D4: U11.B17 (PC12/NAND_DQ4/SDC2_D4); also elsewhere on the board
eMMC-D5: U11.B19 (PC13/NAND_DQ5/SDC2_D5); also elsewhere on the board
eMMC-D6: U11.F17 (PC14/NAND_DQ6/SDC2_D6); also elsewhere on the board
eMMC-D7: U11.C19 (PC15/NAND_DQ7/SDC2_D7); also elsewhere on the board
eMMC-RST: U11.H16 (PC16/NAND_DQS/SDC2_RST); also elsewhere on the board

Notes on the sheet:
Bluetooth/wifi uart
WIFI
(GPIOG8=200, GPIOG9=201, GPIOG11=203)
USB OTG
PC1 was connected to N_VBUSEN but I don't think it was used.
GPIOG11 (was on gpio header)
LORAUX was previously on GPIOC0 SRR_NRST was previously on GPIOC3
(GPIOC0=64, GPIOC1=65, GPIOC2=66, GPIOC3=67)

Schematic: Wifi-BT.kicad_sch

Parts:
U19: ESP32-C6-Board; ESP32Hosted-C6-Board

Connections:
GND: U19.9 (GND); also elsewhere on the board
VDD_SYS_3.3V: U19.1 (VDD33); also elsewhere on the board
WIFI-DataReady: U19.3 (DataReady); also elsewhere on the board
WIFI-EN: U19.2 (EN); also elsewhere on the board
WIFI-HandShake: U19.4 (Handshake); also elsewhere on the board
WIFI-SPI-CS0: U19.8 (CS0); also elsewhere on the board
WIFI-SPI-MISO: U19.6 (MISO); also elsewhere on the board
WIFI-SPI-MOSI: U19.7 (MOSI); also elsewhere on the board
WIFI-SPI-SCLK: U19.5 (SCLK); also elsewhere on the board
